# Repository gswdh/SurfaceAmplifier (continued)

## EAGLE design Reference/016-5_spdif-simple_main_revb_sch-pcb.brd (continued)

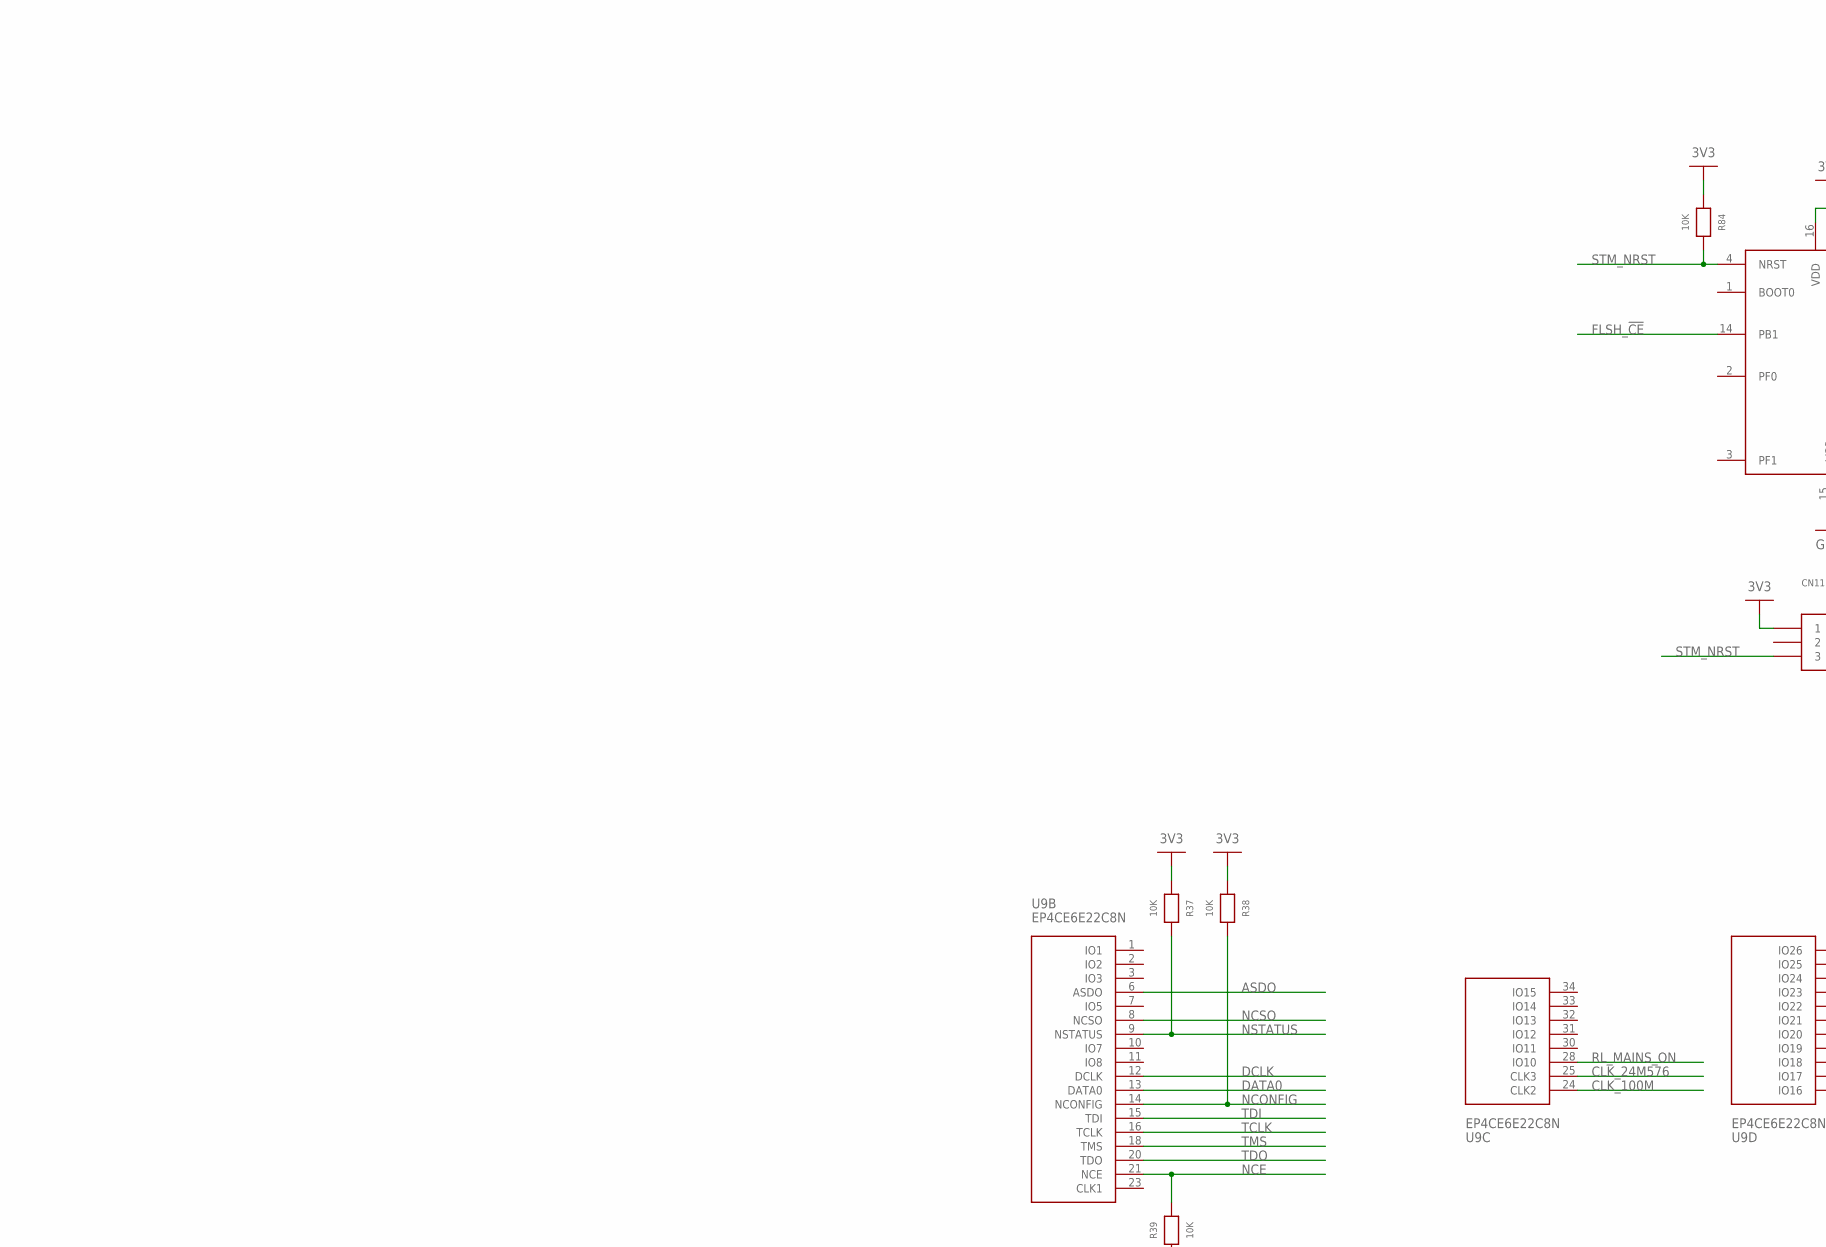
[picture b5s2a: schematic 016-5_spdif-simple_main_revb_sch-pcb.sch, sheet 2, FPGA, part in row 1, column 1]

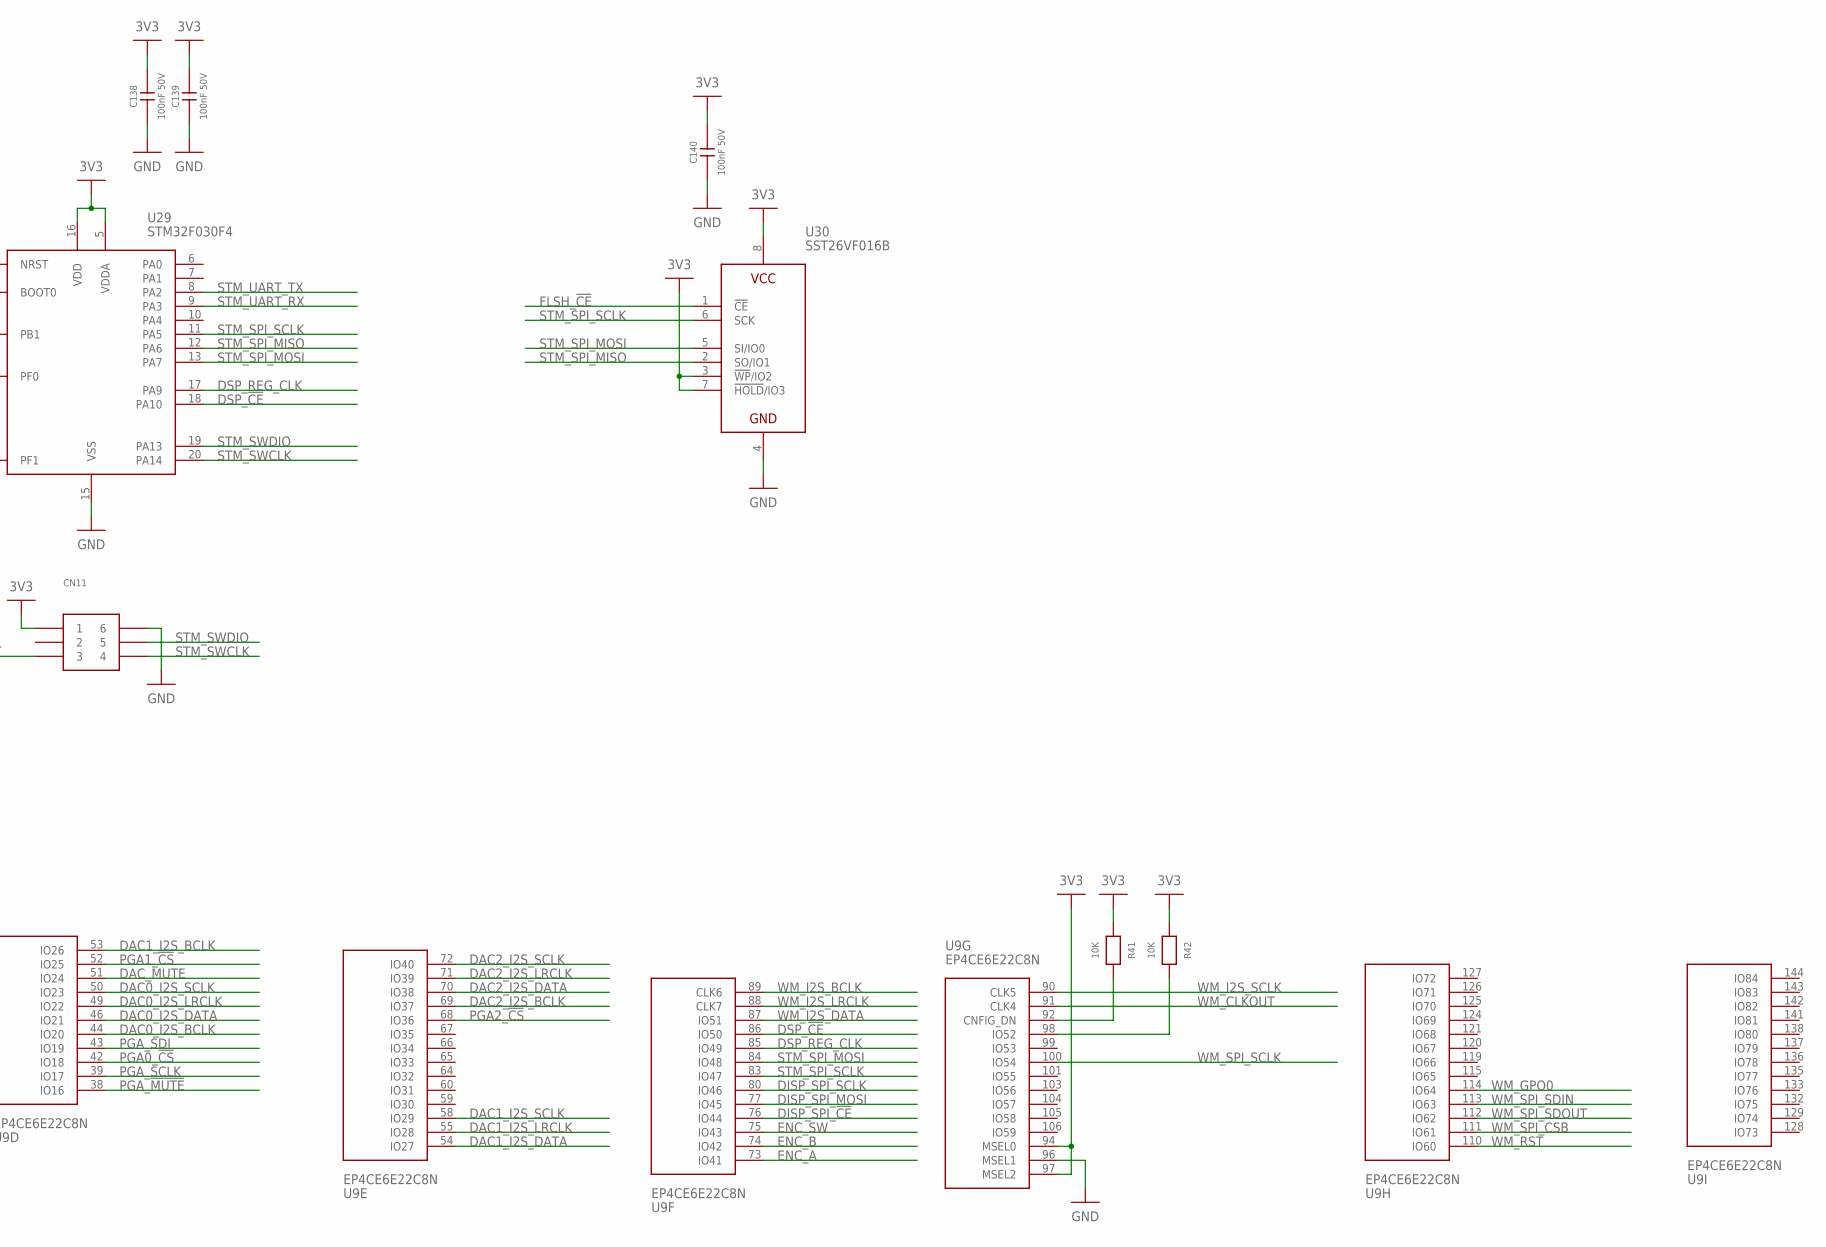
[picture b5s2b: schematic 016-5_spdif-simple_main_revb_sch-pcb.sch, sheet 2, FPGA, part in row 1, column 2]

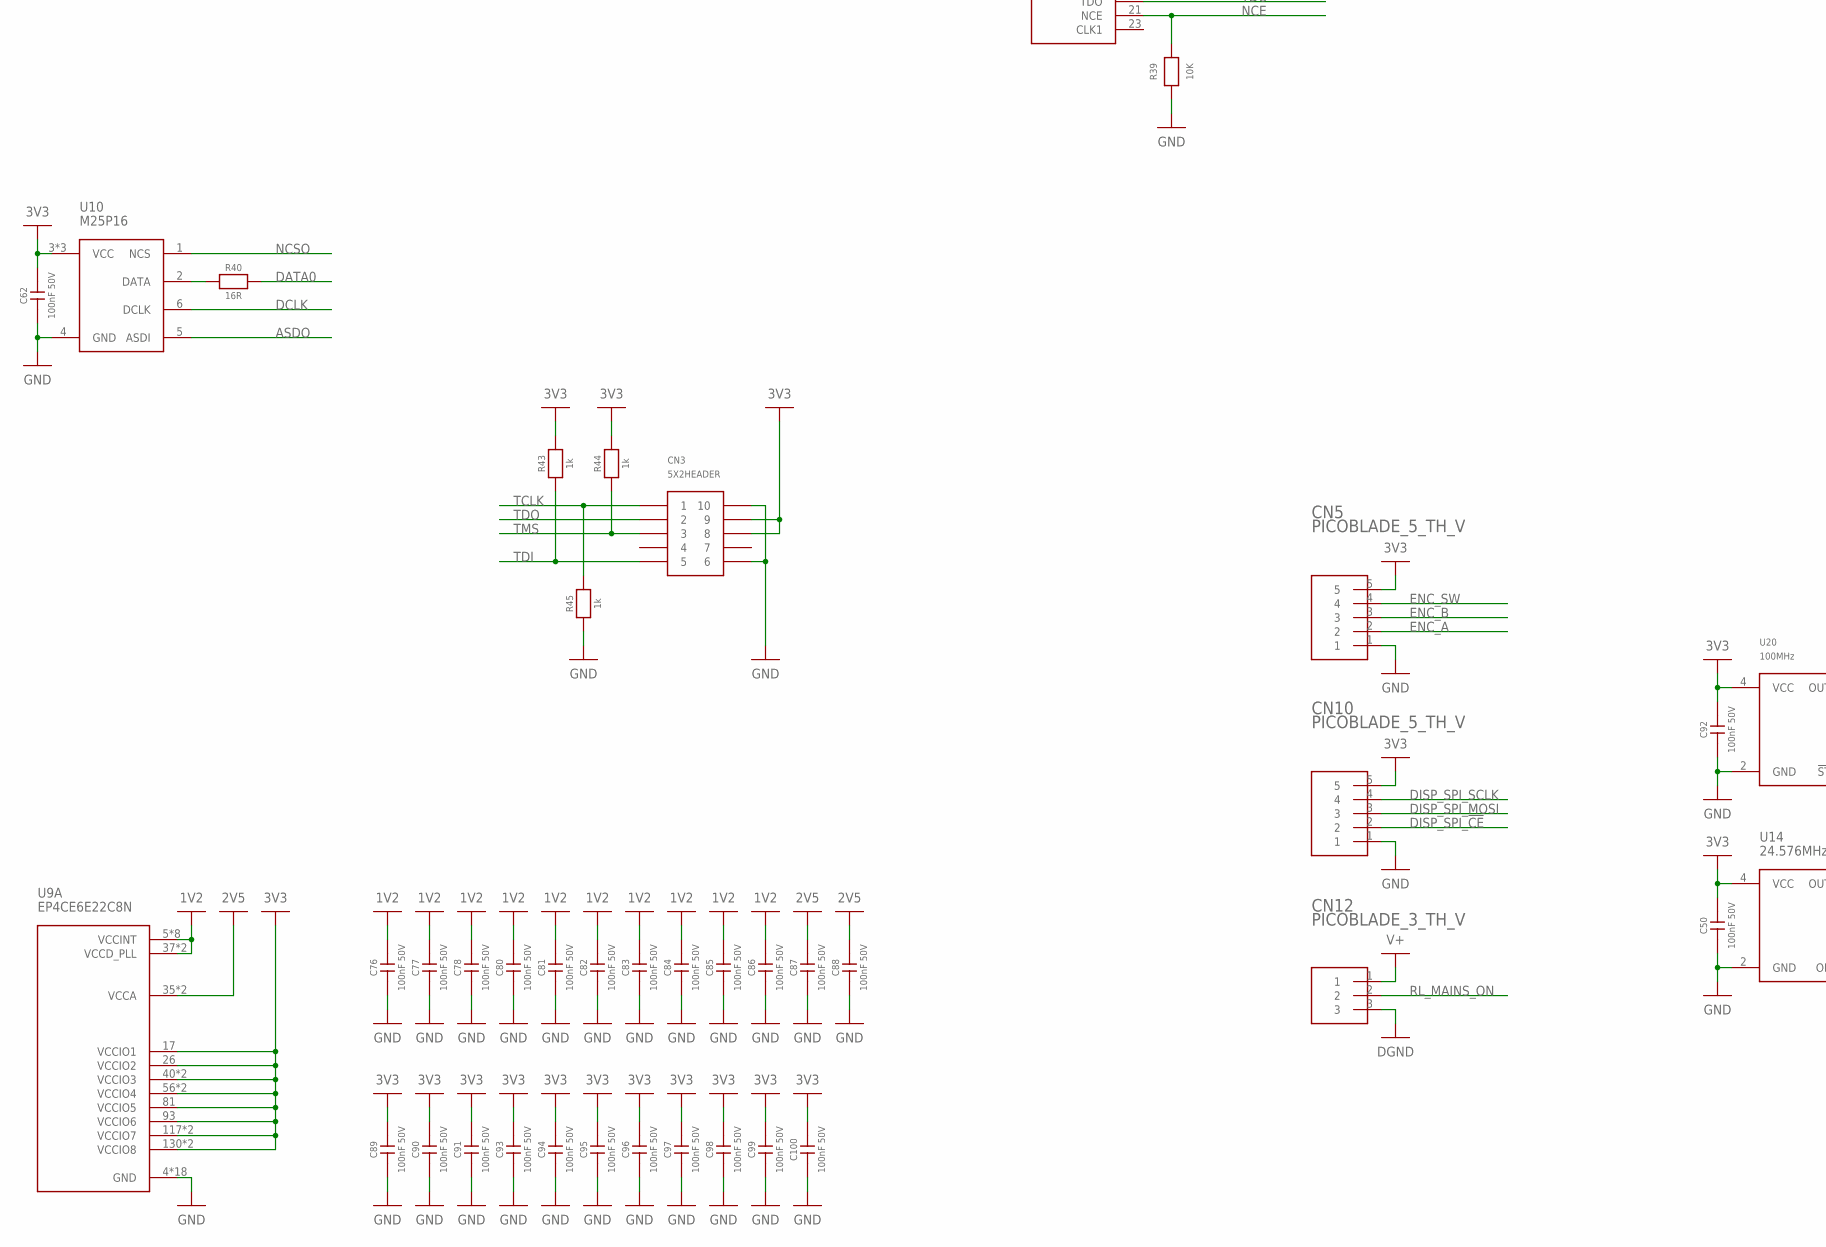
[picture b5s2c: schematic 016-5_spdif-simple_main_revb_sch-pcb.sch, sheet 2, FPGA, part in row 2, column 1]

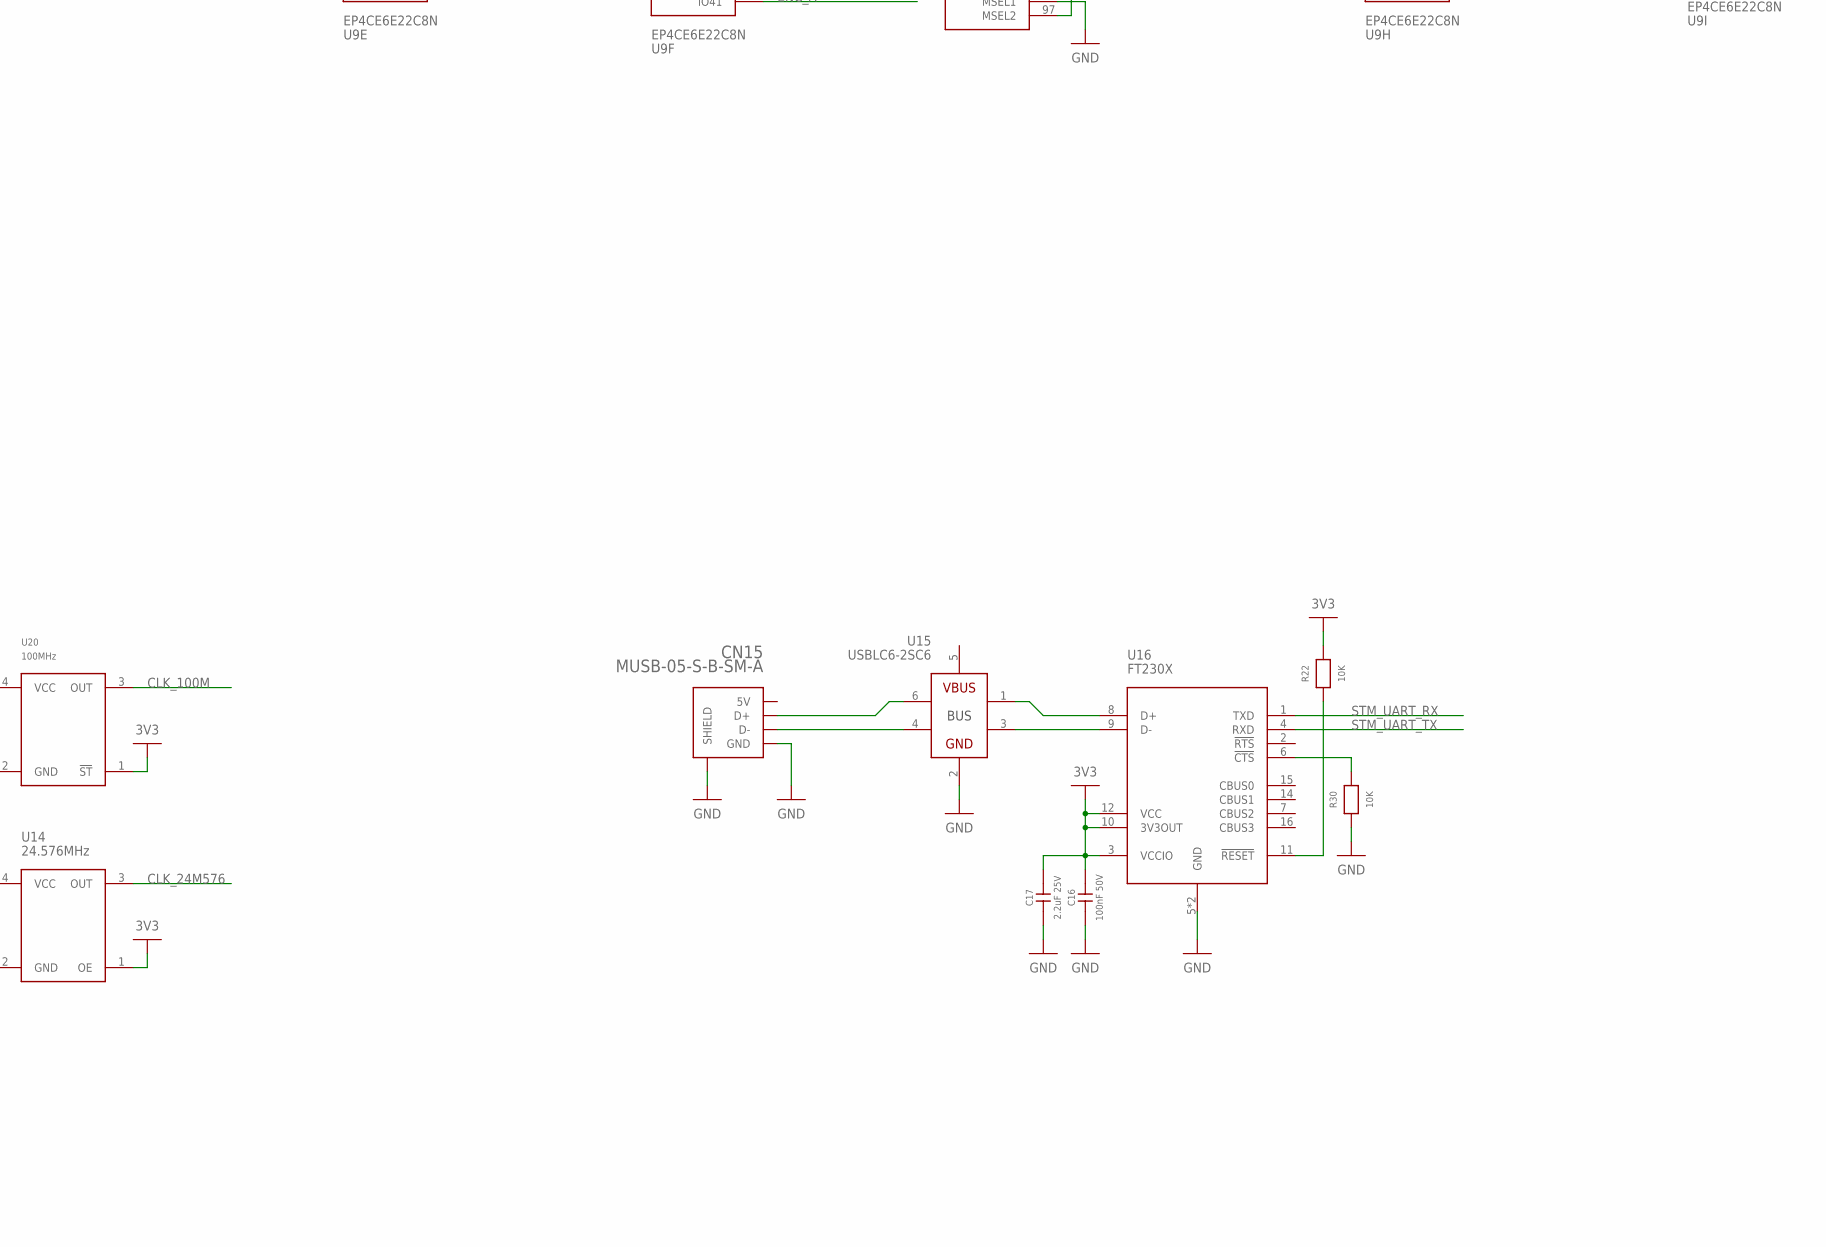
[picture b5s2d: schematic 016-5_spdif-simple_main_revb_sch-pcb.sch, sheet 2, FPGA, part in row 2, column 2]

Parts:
C16, C50, C76, C77, C78, C80, C81, C82, C83, C84, C85, C86, C87, C88, C89, C90, C91, C92, C93, C94, C95, C96, C97, C98, C99, C100, C138, C139, C140: 100nF 50V; 0603; FARNELL 2407338
C17: 2.2uF 25V; 0603; FARNELL 1845734
C62: 100nF 50V; 0603
CN3: 5X2HEADER; 5X2_2.54MMHEADER
CN5, CN10: PICOBLADE_5_TH_V; MOLEX_530470510
CN11: 2X3_HEADER; 2X3HEADER
CN12: PICOBLADE_3_TH_V; MOLEX_530470310
CN15: MUSB-05-S-B-SM-A
R22, R30, R41, R42: 10K; 0603; FARNELL 1469748
R37, R38, R39, R84: 10K; 0603
R40: 16R; 0603
R43, R44, R45: 1k; 0603
U9: EP4CE6E22C8N; QFP144_PP
U10: M25P16; SO8
U14: 24.576MHz; ASEMB
U15: USBLC6-2SC6; SOT23-6
U16: FT230X; SSOP16-4MM
U20: 100MHz; 5X3.2SEAM
U29: STM32F030F4; SSOP20-4.5MM
U30: SST26VF016B; SO8

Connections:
1V2: C76.2, C77.2, C78.2, C80.2, C81.2, C82.2, C83.2, C84.2, C85.2, C86.2, U9.5 (VCCINT), U9.29 (VCCINT), U9.37 (VCCD_PLL), U9.45 (VCCINT), U9.61 (VCCINT), U9.78 (VCCINT), U9.102 (VCCINT), U9.109 (VCCD_PLL), U9.116 (VCCINT), U9.134 (VCCINT); also elsewhere on the board
2V5: C87.2, C88.2, U9.35 (VCCA), U9.107 (VCCA); also elsewhere on the board
3V3: C16.2, C17.2, C50.2, C62.2, C89.2, C90.2, C91.2, C92.2, C93.2, C94.2, C95.2, C96.2, C97.2, C98.2, C99.2, C100.2, C138.2, C139.2, C140.2, CN3.8, CN3.9, CN5.5, CN10.5, CN11.1, R22.2, R37.1, R38.1, R41.1, R42.1, R43.2, R44.2, R84.1, U9.17 (VCCIO1), U9.26 (VCCIO2), U9.40 (VCCIO3), U9.47 (VCCIO3), U9.56 (VCCIO4), U9.62 (VCCIO4), U9.81 (VCCIO5), U9.93 (VCCIO6), U9.94 (MSEL0), U9.97 (MSEL2), U9.117 (VCCIO7), U9.122 (VCCIO7), U9.130 (VCCIO8), U9.139 (VCCIO8), U10.3 (VCC), U10.7 (VCC), U10.8 (VCC), U14.1 (OE), U14.4 (VCC), U16.3 (VCCIO), U16.10 (3V3OUT), U16.12 (VCC), U20.1 (!ST), U20.4 (VCC), U29.5 (VDDA), U29.16 (VDD), U30.3 (!WP!/IO2), U30.7 (!HOLD!/IO3), U30.8 (VCC); also elsewhere on the board
ASDO: U9.6 (ASDO), U10.5 (ASDI)
CLK_24M576: U9.25 (CLK3), U14.3 (OUT)
CLK_100M: U9.24 (CLK2), U20.3 (OUT)
CONF_DN: R41.2, U9.92 (CNFIG_DN)
DAC0_I2S_BCLK: U9.44 (IO20); also elsewhere on the board
DAC0_I2S_DATA: U9.46 (IO21); also elsewhere on the board
DAC0_I2S_LRCLK: U9.49 (IO22); also elsewhere on the board
DAC0_I2S_SCLK: U9.50 (IO23); also elsewhere on the board
DAC1_I2S_BCLK: U9.53 (IO26); also elsewhere on the board
DAC1_I2S_DATA: U9.54 (IO27); also elsewhere on the board
DAC1_I2S_LRCLK: U9.55 (IO28); also elsewhere on the board
DAC1_I2S_SCLK: U9.58 (IO29); also elsewhere on the board
DAC2_I2S_BCLK: U9.69 (IO37); also elsewhere on the board
DAC2_I2S_DATA: U9.70 (IO38); also elsewhere on the board
DAC2_I2S_LRCLK: U9.71 (IO39); also elsewhere on the board
DAC2_I2S_SCLK: U9.72 (IO40); also elsewhere on the board
DAC_MUTE: U9.51 (IO24); also elsewhere on the board
DATA0: R40.2, U9.13 (DATA0)
DCLK: U9.12 (DCLK), U10.6 (DCLK)
DGND: CN12.3
DISP_SPI_!CE: CN10.2, U9.76 (IO44)
DISP_SPI_MOSI: CN10.3, U9.77 (IO45)
DISP_SPI_SCLK: CN10.4, U9.80 (IO46)
DSP_!CE: U9.86 (IO50), U29.18 (PA10)
DSP_REG_CLK: U9.85 (IO49), U29.17 (PA9)
ENC_A: CN5.2, U9.73 (IO41)
ENC_B: CN5.3, U9.74 (IO42)
ENC_SW: CN5.4, U9.75 (IO43)
FLSH_!CE: U29.14 (PB1), U30.1 (!CE)
GND: C16.1, C17.1, C50.1, C62.1, C76.1, C77.1, C78.1, C80.1, C81.1, C82.1, C83.1, C84.1, C85.1, C86.1, C87.1, C88.1, C89.1, C90.1, C91.1, C92.1, C93.1, C94.1, C95.1, C96.1, C97.1, C98.1, C99.1, C100.1, C138.1, C139.1, C140.1, CN3.6, CN3.10, CN5.1, CN10.1, CN11.6, CN15.GND, CN15.SHIELD1 (SHIELD), CN15.SHIELD2 (SHIELD), CN15.SHIELD3 (SHIELD), CN15.SHIELD4 (SHIELD), R30.1, R39.1, R45.1, U9.4 (GND), U9.19 (GND), U9.22 (GND), U9.27 (GND), U9.36 (GND), U9.41 (GND), U9.48 (GND), U9.57 (GND), U9.63 (GND), U9.79 (GND), U9.82 (GND), U9.95 (GND), U9.96 (MSEL1), U9.108 (GND), U9.118 (GND), U9.123 (GND), U9.131 (GND), U9.140 (GND), U9.GND, U10.4 (GND), U14.2 (GND), U15.2 (GND), U16.5 (GND), U16.13 (GND), U20.2 (GND), U29.15 (VSS), U30.4 (GND); also elsewhere on the board
INIT_DONE: R42.2, U9.98 (IO52)
unnamed: R40.1, U10.2 (DATA)
unnamed: CN15.D-, U15.4 (D-OUT)
unnamed: CN15.D+, U15.6 (D+_OUT)
unnamed: U15.3 (D-_IN), U16.9 (D-)
unnamed: U15.1 (D+_IN), U16.8 (D+)
unnamed: R22.1, U16.11 (!RESET)
unnamed: R30.2, U16.6 (!CTS)
NCE: R39.2, U9.21 (NCE)
NCONFIG: R38.2, U9.14 (NCONFIG)
NCSO: U9.8 (NCSO), U10.1 (NCS)
NSTATUS: R37.2, U9.9 (NSTATUS)
PGA0_!CS: U9.42 (IO18); also elsewhere on the board
PGA1_!CS: U9.52 (IO25); also elsewhere on the board
PGA2_!CS: U9.68 (IO36); also elsewhere on the board
PGA_!MUTE: U9.38 (IO16); also elsewhere on the board
PGA_SCLK: U9.39 (IO17); also elsewhere on the board
PGA_SDI: U9.43 (IO19); also elsewhere on the board
RL_MAINS_ON: CN12.2, U9.28 (IO10)
STM_NRST: CN11.3, R84.2, U29.4 (NRST)
STM_SPI_MISO: U29.12 (PA6), U30.2 (SO/IO1)
STM_SPI_MOSI: U9.84 (IO48), U29.13 (PA7), U30.5 (SI/IO0)
STM_SPI_SCLK: U9.83 (IO47), U29.11 (PA5), U30.6 (SCK)
STM_SWCLK: CN11.4, U29.20 (PA14)
STM_SWDIO: CN11.5, U29.19 (PA13)
STM_UART_RX: U16.1 (TXD), U29.9 (PA3)
STM_UART_TX: U16.4 (RXD), U29.8 (PA2)
TCLK: CN3.1, R45.2, U9.16 (TCLK)
TDI: CN3.5, R43.1, U9.15 (TDI)
TDO: CN3.2, U9.20 (TDO)
TMS: CN3.3, R44.1, U9.18 (TMS)
V+: CN12.1; also elsewhere on the board
WM_CLKOUT: U9.91 (CLK4); also elsewhere on the board
WM_GPO0: U9.114 (IO64); also elsewhere on the board
WM_I2S_BCLK: U9.89 (CLK6); also elsewhere on the board
WM_I2S_DATA: U9.87 (IO51); also elsewhere on the board
WM_I2S_LRCLK: U9.88 (CLK7); also elsewhere on the board
WM_I2S_SCLK: U9.90 (CLK5); also elsewhere on the board
WM_RST: U9.110 (IO60); also elsewhere on the board
WM_SPI_CSB: U9.111 (IO61); also elsewhere on the board
WM_SPI_SCLK: U9.100 (IO54); also elsewhere on the board
WM_SPI_SDIN: U9.113 (IO63); also elsewhere on the board
WM_SPI_SDOUT: U9.112 (IO62); also elsewhere on the board
